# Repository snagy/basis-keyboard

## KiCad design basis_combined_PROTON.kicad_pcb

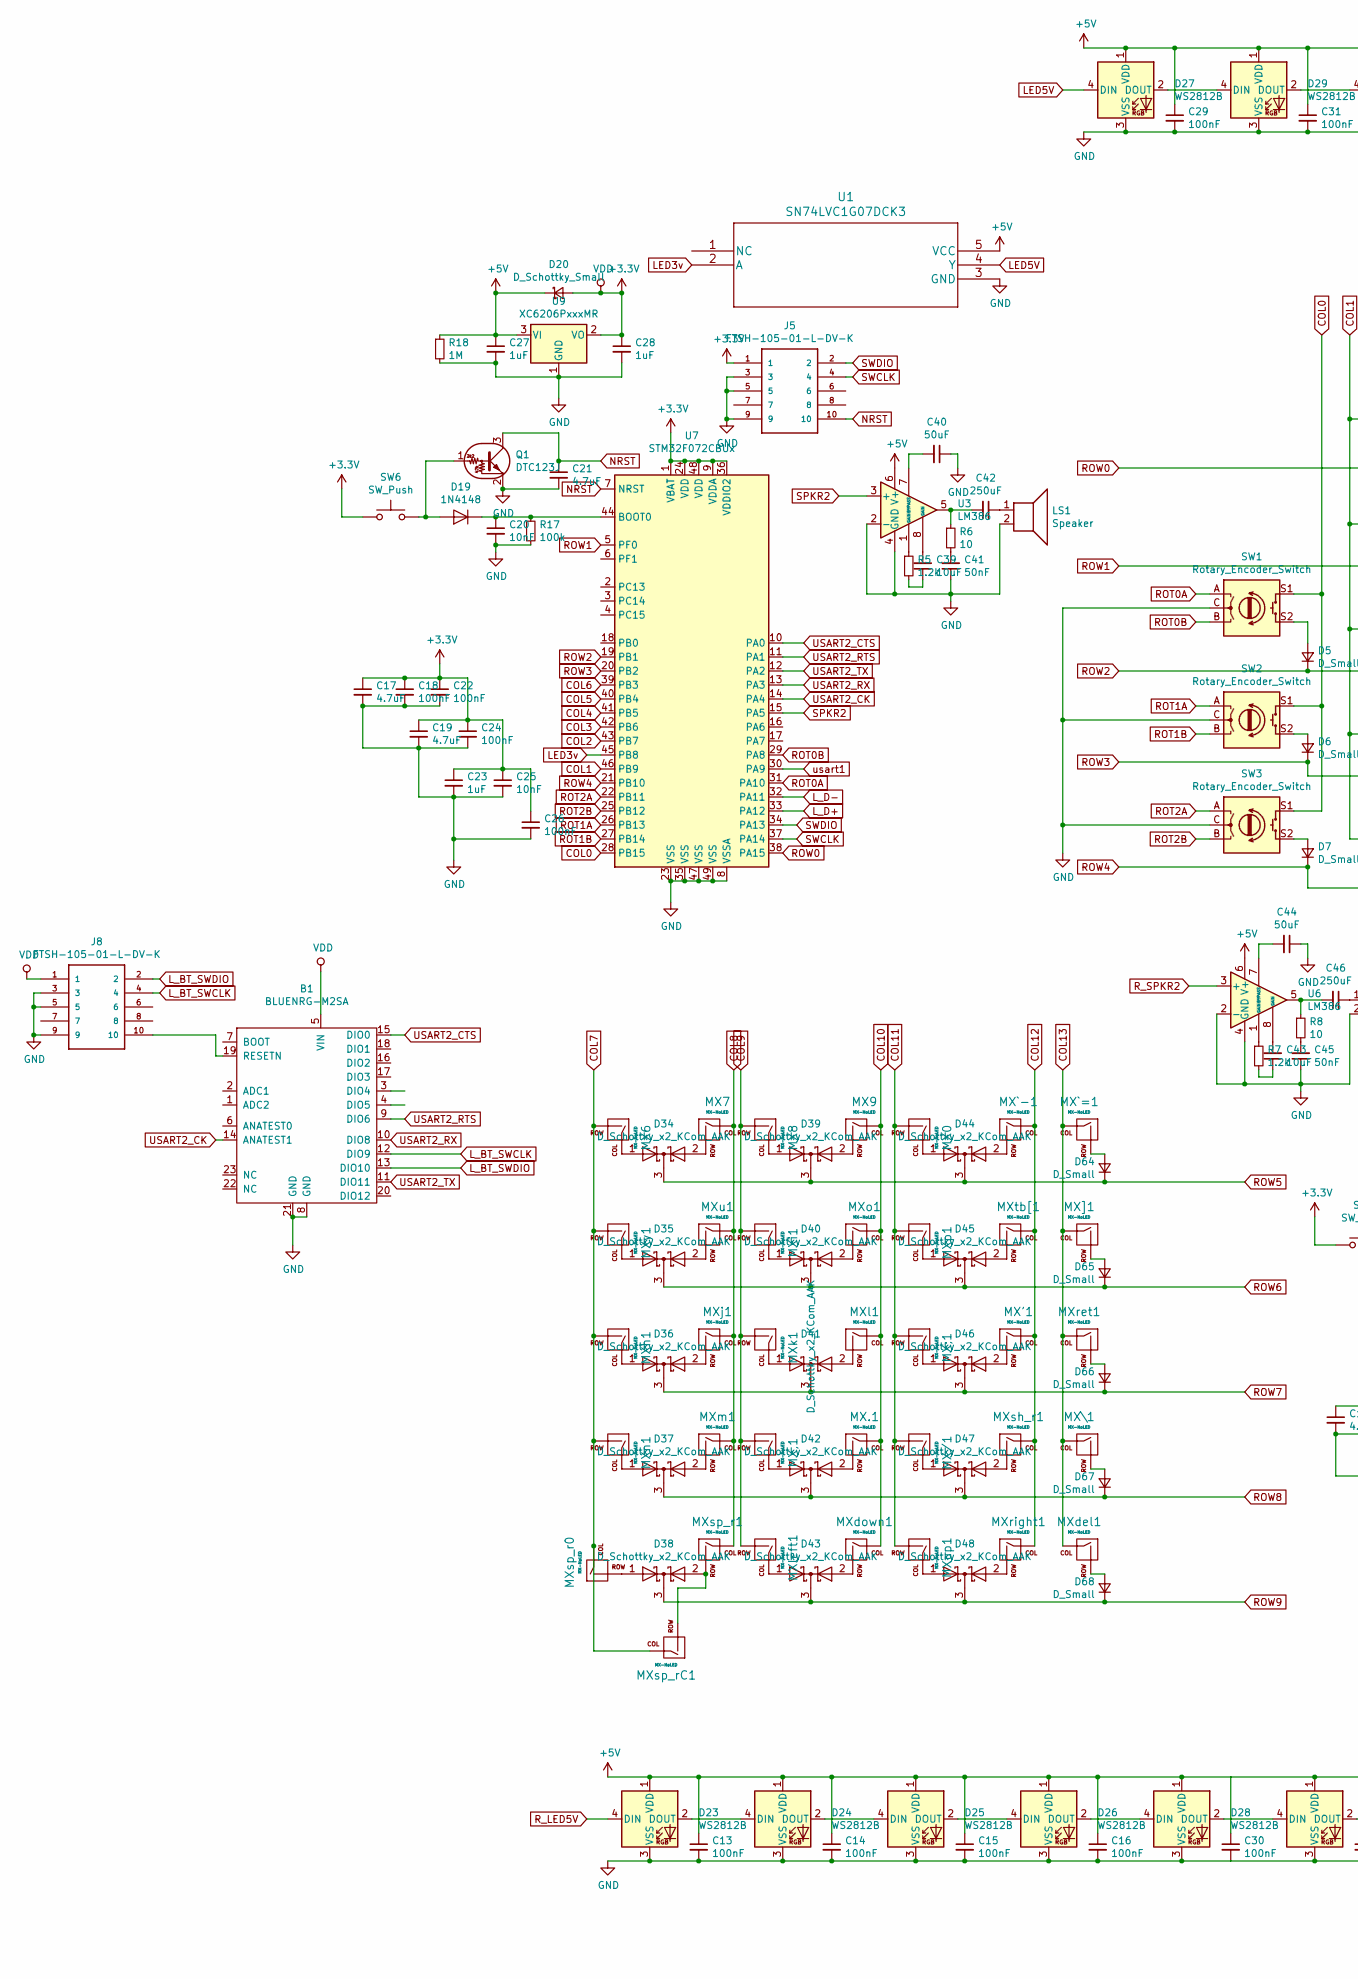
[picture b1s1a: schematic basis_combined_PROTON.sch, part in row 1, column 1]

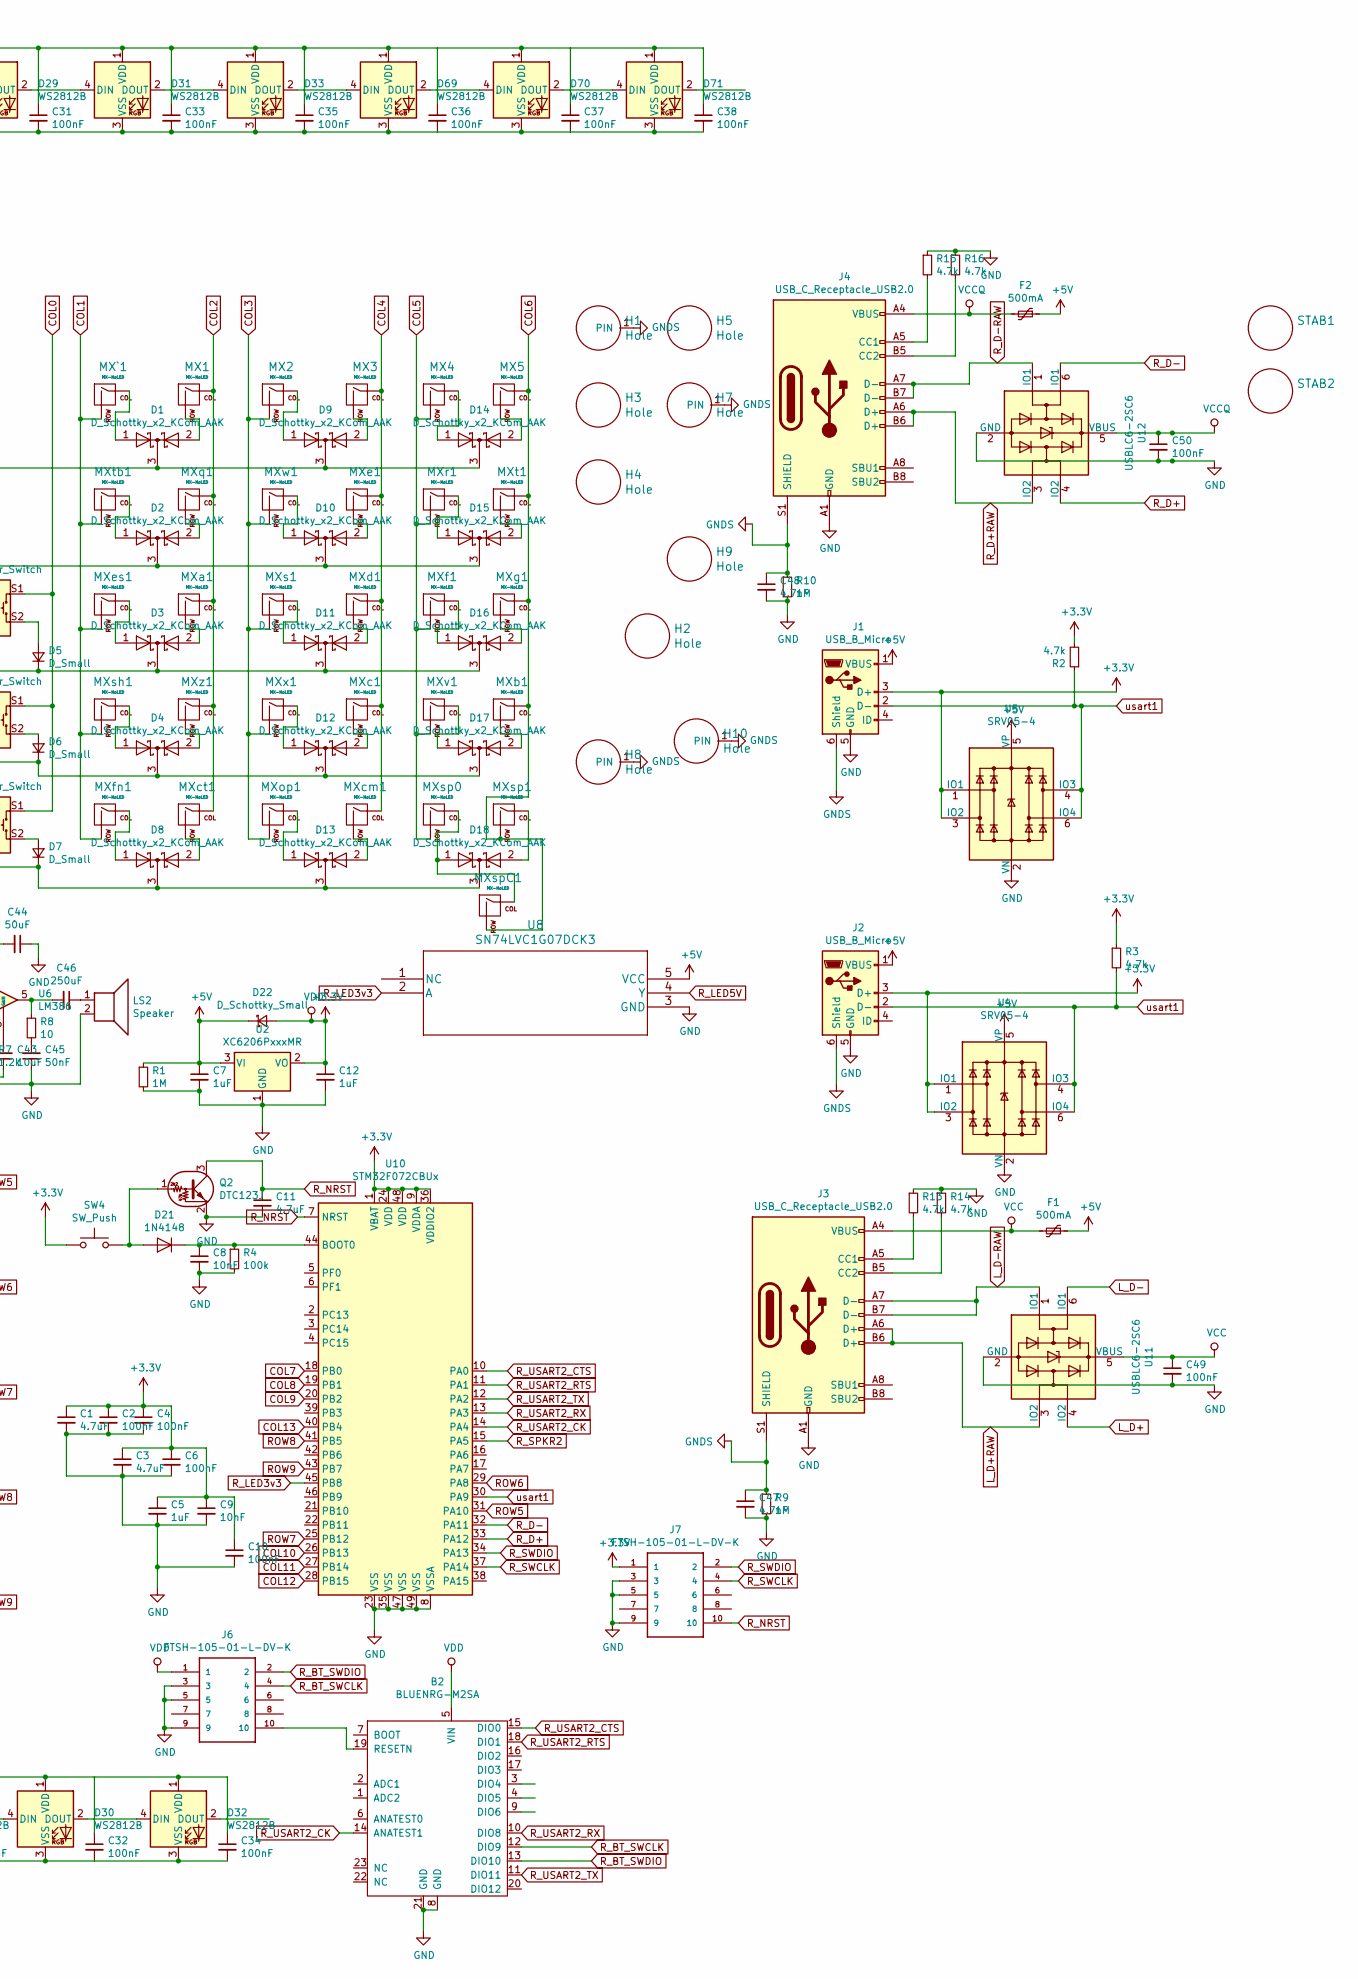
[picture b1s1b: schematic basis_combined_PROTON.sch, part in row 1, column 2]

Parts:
B1, B2: BLUENRG-M2SA
C1, C3, C11, C17, C19, C21: 4.7uF; C_0402_1005Metric
C2, C4, C6, C10, C13, C14, C15, C16, C18, C22, C24, C26, C29, C30, C31, C32, C33, C34, C35, C36, C37, C38, C49, C50: 100nF; C_0402_1005Metric
C5, C7, C12, C23, C27, C28: 1uF; C_0402_1005Metric
C8, C9, C20, C25: 10nF; C_0402_1005Metric
C39, C43: 10uF; C_0402_1005Metric
C40, C44: 50uF; C_0402_1005Metric
C41, C45: 50nF; C_0402_1005Metric
C42, C46: 250uF; C_0402_1005Metric
C47, C48: 4.7nF; C_0402_1005Metric
D1, D2, D3, D4, D8, D9, D10, D11, D12, D13, D14, D15, D16, D17, D18, D34, D35, D36, D37, D38, D39, D40, D41, D42, D43, D44, D45, D46, D47, D48: D_Schottky_x2_KCom_AAK; D_SOT-23_AAK
D5, D6, D7, D64, D65, D66, D67, D68: D_Small; D_SOD-123
D19, D21: 1N4148; D_SOD-123
D20, D22: D_Schottky_Small; D_SOD-123
D23, D24, D25, D26, D27, D28, D29, D30, D31, D32, D33, D69, D70, D71: WS2812B; LED_WS2812B_PLCC4_5.0x5.0mm_P3.2mm
F1, F2: 500mA; Fuse_1206_3216Metric
H1, H2, H3, H4, H5, H7, H8, H9, H10: Hole; Mounting_Wuerth_WA-SMSI-M2_H3.5mm_9774035243
J1, J2: USB_B_Micro; MOLEX_47642-0001
J3, J4: USB_C_Receptacle_USB2.0; USB_C_Receptacle_Hirose_CX90M-16P
J5, J6, J7, J8: FTSH-105-01-L-DV-K; SAMTEC_FTSH-105-01-L-DV-K
LS1, LS2: Speaker; cms-151103-16sp
MX0, MX1, MX2, MX3, MX4, MX5, MX6, MX7, MX8, MX9, MX.1: MX-NoLED; Kailh_socket_MX_optional
MX'1: MX-NoLED; Kailh_socket_MX_optional
MX,1: MX-NoLED; Kailh_socket_MX_optional
MX/1: MX-NoLED; Kailh_socket_MX_optional
MX;1: MX-NoLED; Kailh_socket_MX_optional
MX\1: MX-NoLED; Kailh_socket_MX_optional
MX]1: MX-NoLED; Kailh_socket_MX_optional
MX`1: MX-NoLED; Kailh_socket_MX_optional
MX`-1: MX-NoLED; Kailh_socket_MX_optional
MX`=1: MX-NoLED; Kailh_socket_MX_optional
MXa1: MX-NoLED; Kailh_socket_MX_optional
MXb1: MX-NoLED; Kailh_socket_MX_optional
MXc1: MX-NoLED; Kailh_socket_MX_optional
MXcm1: MX-NoLED; Kailh_socket_MX_optional
MXct1: MX-NoLED; Kailh_socket_MX_optional
MXd1: MX-NoLED; Kailh_socket_MX_optional
MXdel1: MX-NoLED; Kailh_socket_MX_optional
MXdown1: MX-NoLED; Kailh_socket_MX_optional
MXe1: MX-NoLED; Kailh_socket_MX_optional
MXes1: MX-NoLED; Kailh_socket_MX_optional
MXf1: MX-NoLED; Kailh_socket_MX_optional
MXfn1: MX-NoLED; Kailh_socket_MX_optional
MXg1: MX-NoLED; Kailh_socket_MX_optional
MXh1: MX-NoLED; Kailh_socket_MX_optional
MXi1: MX-NoLED; Kailh_socket_MX_optional
MXj1: MX-NoLED; Kailh_socket_MX_optional
MXk1: MX-NoLED; Kailh_socket_MX_optional
MXl1: MX-NoLED; Kailh_socket_MX_optional
MXleft1: MX-NoLED; Kailh_socket_MX_optional
MXm1: MX-NoLED; Kailh_socket_MX_optional
MXn1: MX-NoLED; Kailh_socket_MX_optional
MXo1: MX-NoLED; Kailh_socket_MX_optional
MXop1: MX-NoLED; Kailh_socket_MX_optional
MXp1: MX-NoLED; Kailh_socket_MX_optional
MXq1: MX-NoLED; Kailh_socket_MX_optional
MXr1: MX-NoLED; Kailh_socket_MX_optional
MXret1: MX-NoLED; Kailh_socket_MX_optional
MXright1: MX-NoLED; Kailh_socket_MX_optional
MXs1: MX-NoLED; Kailh_socket_MX_optional
MXsh1: MX-NoLED; Kailh_socket_MX_optional
MXsh_r1: MX-NoLED; Kailh_socket_MX_optional
MXsp0, MXsp1: MX-NoLED; Kailh_socket_MX_optional
MXspC1: MX-NoLED; Kailh_socket_MX_optional
MXsp_r0, MXsp_r1: MX-NoLED; Kailh_socket_MX_optional
MXsp_rC1: MX-NoLED; Kailh_socket_MX_optional
MXt1: MX-NoLED; Kailh_socket_MX_optional
MXtb1: MX-NoLED; Kailh_socket_MX_optional
MXtb[1: MX-NoLED; Kailh_socket_MX_optional
MXu1: MX-NoLED; Kailh_socket_MX_optional
MXup1: MX-NoLED; Kailh_socket_MX_optional
MXv1: MX-NoLED; Kailh_socket_MX_optional
MXw1: MX-NoLED; Kailh_socket_MX_optional
MXx1: MX-NoLED; Kailh_socket_MX_optional
MXy1: MX-NoLED; Kailh_socket_MX_optional
MXz1: MX-NoLED; Kailh_socket_MX_optional
Q1, Q2: DTC123J; SOT-723
R1, R9, R10, R18: 1M; R_0402_1005Metric
R2, R3, R13, R14, R15, R16: 4.7k; R_0402_1005Metric
R4, R17: 100k; R_0402_1005Metric
R5, R7: 1.2k; R_0402_1005Metric
R6, R8: 10; R_0402_1005Metric
STAB1, STAB2: Hole; Stabilizer_MX_2u
SW1, SW2, SW3: Rotary_Encoder_Switch; RotaryEncoder_Alps_EC11E-Switch_Vertical_H20mm
SW4, SW6: SW_Push; SKQG-1155865
U1, U8: SN74LVC1G07DCK3
U2, U9: XC6206PxxxMR; SOT-23
U3, U6: LM386; SOIC-8_3.9x4.9mm_P1.27mm
U4, U5: SRV05-4; SOT-23-6
U7, U10: STM32F072CBUx; QFN-48-1EP_7x7mm_P0.5mm_EP5.6x5.6mm
U11, U12: USBLC6-2SC6; SOT-666

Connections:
+3V3: B1.5 (VIN), B2.5 (VIN), C1.1, C2.1, C3.1, C4.1, C5.1, C6.1, C9.1, C10.1, C12.1, C17.1, C18.1, C19.1, C22.1, C23.1, C24.1, C25.1, C26.1, C28.1, D20.2 (A), D22.2 (A), J1.3 (D+), J2.3 (D+), J5.1, J6.1, J7.1, J8.1, R2.2, R3.1, SW4.1, SW6.1, U2.2 (VO), U4.1 (IO1), U4.3 (IO2), U5.1 (IO1), U5.3 (IO2), U7.1 (VBAT), U7.9 (VDDA), U7.24 (VDD), U7.36 (VDDIO2), U7.48 (VDD), U9.2 (VO), U10.1 (VBAT), U10.9 (VDDA), U10.24 (VDD), U10.36 (VDDIO2), U10.48 (VDD)
+5V: C7.1, C13.1, C14.1, C15.1, C16.1, C27.1, C29.1, C30.1, C31.1, C32.1, C33.1, C34.1, C35.1, C36.1, C37.1, C38.1, D20.1 (K), D22.1 (K), D23.1 (VDD), D24.1 (VDD), D25.1 (VDD), D26.1 (VDD), D27.1 (VDD), D28.1 (VDD), D29.1 (VDD), D30.1 (VDD), D31.1 (VDD), D32.1 (VDD), D33.1 (VDD), D69.1 (VDD), D70.1 (VDD), D71.1 (VDD), F1.1, F2.1, J1.1 (VBUS), J2.1 (VBUS), R1.1, R18.1, U1.5 (VCC), U2.3 (VI), U3.6 (V+), U4.5 (VP), U5.5 (VP), U6.6 (V+), U8.5 (VCC), U9.3 (VI)
COL0: SW1.S1, SW2.S1, SW3.S1, U7.28 (PB15)
COL1: MX`1.2 (ROW), MXes1.2 (ROW), MXfn1.2 (ROW), MXsh1.2 (ROW), MXtb1.2 (ROW), U7.46 (PB9)
COL2: MX1.1 (COL), MXa1.1 (COL), MXct1.1 (COL), MXq1.1 (COL), MXz1.1 (COL), U7.43 (PB7)
COL3: MX2.2 (ROW), MXop1.2 (ROW), MXs1.2 (ROW), MXw1.2 (ROW), MXx1.2 (ROW), U7.42 (PB6)
COL4: MX3.1 (COL), MXc1.1 (COL), MXcm1.1 (COL), MXd1.1 (COL), MXe1.1 (COL), U7.41 (PB5)
COL5: MX4.2 (ROW), MXf1.2 (ROW), MXr1.2 (ROW), MXsp0.2 (ROW), MXv1.2 (ROW), U7.40 (PB4)
COL6: MX5.1 (COL), MXb1.1 (COL), MXg1.1 (COL), MXsp1.2 (ROW), MXspC1.2 (ROW), MXt1.1 (COL), U7.39 (PB3)
COL7: MX6.2 (ROW), MXh1.2 (ROW), MXn1.2 (ROW), MXsp_r0.1 (COL), MXsp_rC1.1 (COL), MXy1.2 (ROW), U10.18 (PB0)
COL8: MX7.1 (COL), MXj1.1 (COL), MXm1.1 (COL), MXsp_r1.1 (COL), MXu1.1 (COL), U10.19 (PB1)
COL9: MX8.2 (ROW), MX,1.2 (ROW), MXi1.2 (ROW), MXk1.2 (ROW), MXleft1.2 (ROW), U10.20 (PB2)
COL10: MX9.1 (COL), MX.1.1 (COL), MXdown1.1 (COL), MXl1.1 (COL), MXo1.1 (COL), U10.26 (PB13)
COL11: MX0.2 (ROW), MX/1.2 (ROW), MX;1.2 (ROW), MXp1.2 (ROW), MXup1.2 (ROW), U10.27 (PB14)
COL12: MX'1.1 (COL), MX`-1.1 (COL), MXright1.1 (COL), MXsh_r1.1 (COL), MXtb[1.1 (COL), U10.28 (PB15)
COL13: MX\1.1 (COL), MX]1.1 (COL), MX`=1.1 (COL), MXdel1.1 (COL), MXret1.1 (COL), U10.40 (PB4)
GND: B1.8 (GND), B1.21 (GND), B2.8 (GND), B2.21 (GND), C1.2, C2.2, C3.2, C4.2, C5.2, C6.2, C7.2, C8.2, C9.2, C10.2, C11.2, C12.2, C13.2, C14.2, C15.2, C16.2, C17.2, C18.2, C19.2, C20.2, C21.2, C22.2, C23.2, C24.2, C25.2, C26.2, C27.2, C28.2, C29.2, C30.2, C31.2, C32.2, C33.2, C34.2, C35.2, C36.2, C37.2, C38.2, C40.1, C41.1, C44.1, C45.1, C47.2, C48.2, C49.2, C50.2, D23.3 (VSS), D24.3 (VSS), D25.3 (VSS), D26.3 (VSS), D27.3 (VSS), D28.3 (VSS), D29.3 (VSS), D30.3 (VSS), D31.3 (VSS), D32.3 (VSS), D33.3 (VSS), D69.3 (VSS), D70.3 (VSS), D71.3 (VSS), J1.5 (GND), J2.5 (GND), J3.A1 (GND), J3.A12 (GND), J3.B1 (GND), J3.B12 (GND), J4.A1 (GND), J4.A12 (GND), J4.B1 (GND), J4.B12 (GND), J5.3, J5.5, J5.9, J6.3, J6.5, J6.9, J7.3, J7.5, J7.9, J8.3, J8.5, J8.9, LS1.2, LS2.2, Q1.2 (E), Q2.2 (E), R1.2, R4.2, R9.2, R10.2, R13.1, R14.1, R15.1, R16.1, R17.2, R18.2, SW1.C, SW2.C, SW3.C, U1.3 (GND), U2.1 (GND), U3.2 (-), U3.4 (GND), U4.2 (VN), U5.2 (VN), U6.2 (-), U6.4 (GND), U7.8 (VSSA), U7.23 (VSS), U7.35 (VSS), U7.47 (VSS), U7.49 (VSS), U8.3 (GND), U9.1 (GND), U10.8 (VSSA), U10.23 (VSS), U10.35 (VSS), U10.47 (VSS), U10.49 (VSS), U11.2 (GND), U12.2 (GND)
GNDS: C47.1, C48.1, H1.1, H7.1, H8.1, H10.1, J1.6 (Shield), J2.6 (Shield), J3.S1 (SHIELD), J4.S1 (SHIELD), R9.1, R10.1
LED3v: U1.2 (A), U7.45 (PB8)
LED5V: D27.4 (DIN), U1.4 (Y)
L_BT_SWCLK: B1.12 (DIO9), J8.4
L_BT_SWDIO: B1.13 (DIO10), J8.2
L_D+: U7.33 (PA12), U11.4 (IO2)
L_D+RAW: J3.A6 (D+), J3.B6 (D+), U11.3 (IO2)
L_D-: U7.32 (PA11), U11.6 (IO1)
L_D-RAW: J3.A7 (D-), J3.B7 (D-), U11.1 (IO1)
NRST: C21.1, J5.10, Q1.3 (C), U7.7 (NRST)
unnamed: B1.19 (RESETN), J8.10
unnamed: B2.19 (RESETN), J6.10
unnamed: C8.1, D21.1 (K), R4.1, U10.44 (BOOT0)
unnamed: C20.1, D19.1 (K), R17.1, U7.44 (BOOT0)
unnamed: C39.1, R5.2
unnamed: C39.2, U3.8 (GAIN)
unnamed: C40.2, U3.7 (BYPASS)
unnamed: C41.2, R6.2
unnamed: C42.1, LS1.1
unnamed: C42.2, R6.1, U3.5
unnamed: C43.1, R7.2
unnamed: C43.2, U6.8 (GAIN)
unnamed: C44.2, U6.7 (BYPASS)
unnamed: C45.2, R8.2
unnamed: C46.1, LS2.1
unnamed: C46.2, R8.1, U6.5
unnamed: D1.1 (A), MX`1.1 (COL)
unnamed: D1.2 (A), MX1.2 (ROW)
unnamed: D2.1 (A), MXtb1.1 (COL)
unnamed: D2.2 (A), MXq1.2 (ROW)
unnamed: D3.1 (A), MXes1.1 (COL)
unnamed: D3.2 (A), MXa1.2 (ROW)
unnamed: D4.1 (A), MXsh1.1 (COL)
unnamed: D4.2 (A), MXz1.2 (ROW)
unnamed: D5.2 (A), SW1.S2
unnamed: D6.2 (A), SW2.S2
unnamed: D7.2 (A), SW3.S2
unnamed: D8.1 (A), MXfn1.1 (COL)
unnamed: D8.2 (A), MXct1.2 (ROW)
unnamed: D9.1 (A), MX2.1 (COL)
unnamed: D9.2 (A), MX3.2 (ROW)
unnamed: D10.1 (A), MXw1.1 (COL)
unnamed: D10.2 (A), MXe1.2 (ROW)
unnamed: D11.1 (A), MXs1.1 (COL)
unnamed: D11.2 (A), MXd1.2 (ROW)
unnamed: D12.1 (A), MXx1.1 (COL)
unnamed: D12.2 (A), MXc1.2 (ROW)
unnamed: D13.1 (A), MXop1.1 (COL)
unnamed: D13.2 (A), MXcm1.2 (ROW)
unnamed: D14.1 (A), MX4.1 (COL)
unnamed: D14.2 (A), MX5.2 (ROW)
unnamed: D15.1 (A), MXr1.1 (COL)
unnamed: D15.2 (A), MXt1.2 (ROW)
unnamed: D16.1 (A), MXf1.1 (COL)
unnamed: D16.2 (A), MXg1.2 (ROW)
unnamed: D17.1 (A), MXv1.1 (COL)
unnamed: D17.2 (A), MXb1.2 (ROW)
unnamed: D18.1 (A), MXsp0.1 (COL), MXspC1.1 (COL)
unnamed: D18.2 (A), MXsp1.1 (COL)
unnamed: D19.2 (A), Q1.1 (B), SW6.2
unnamed: D21.2 (A), Q2.1 (B), SW4.2
unnamed: D23.2 (DOUT), D24.4 (DIN)
unnamed: D24.2 (DOUT), D25.4 (DIN)
unnamed: D25.2 (DOUT), D26.4 (DIN)
unnamed: D26.2 (DOUT), D28.4 (DIN)
unnamed: D27.2 (DOUT), D29.4 (DIN)
unnamed: D28.2 (DOUT), D30.4 (DIN)
unnamed: D29.2 (DOUT), D31.4 (DIN)
unnamed: D30.2 (DOUT), D32.4 (DIN)
unnamed: D31.2 (DOUT), D33.4 (DIN)
unnamed: D33.2 (DOUT), D69.4 (DIN)
unnamed: D34.1 (A), MX6.1 (COL)
unnamed: D34.2 (A), MX7.2 (ROW)
unnamed: D35.1 (A), MXy1.1 (COL)
unnamed: D35.2 (A), MXu1.2 (ROW)
unnamed: D36.1 (A), MXh1.1 (COL)
unnamed: D36.2 (A), MXj1.2 (ROW)
unnamed: D37.1 (A), MXn1.1 (COL)
unnamed: D37.2 (A), MXm1.2 (ROW)
unnamed: D38.1 (A), MXsp_r0.2 (ROW)
unnamed: D38.2 (A), MXsp_r1.2 (ROW), MXsp_rC1.2 (ROW)
unnamed: D39.1 (A), MX8.1 (COL)
unnamed: D39.2 (A), MX9.2 (ROW)
unnamed: D40.1 (A), MXi1.1 (COL)
unnamed: D40.2 (A), MXo1.2 (ROW)
unnamed: D41.1 (A), MXk1.1 (COL)
unnamed: D41.2 (A), MXl1.2 (ROW)
unnamed: D42.1 (A), MX,1.1 (COL)
unnamed: D42.2 (A), MX.1.2 (ROW)
unnamed: D43.1 (A), MXleft1.1 (COL)
unnamed: D43.2 (A), MXdown1.2 (ROW)
unnamed: D44.1 (A), MX0.1 (COL)
unnamed: D44.2 (A), MX`-1.2 (ROW)
unnamed: D45.1 (A), MXp1.1 (COL)
unnamed: D45.2 (A), MXtb[1.2 (ROW)
unnamed: D46.1 (A), MX;1.1 (COL)
unnamed: D46.2 (A), MX'1.2 (ROW)
unnamed: D47.1 (A), MX/1.1 (COL)
unnamed: D47.2 (A), MXsh_r1.2 (ROW)
unnamed: D48.1 (A), MXup1.1 (COL)
unnamed: D48.2 (A), MXright1.2 (ROW)
unnamed: D64.2 (A), MX`=1.2 (ROW)
unnamed: D65.2 (A), MX]1.2 (ROW)
unnamed: D66.2 (A), MXret1.2 (ROW)
unnamed: D67.2 (A), MX\1.2 (ROW)
unnamed: D68.2 (A), MXdel1.2 (ROW)
unnamed: D69.2 (DOUT), D70.4 (DIN)
unnamed: D70.2 (DOUT), D71.4 (DIN)
unnamed: J3.A5 (CC1), R13.2
unnamed: J3.B5 (CC2), R14.2
unnamed: J4.A5 (CC1), R15.2
unnamed: J4.B5 (CC2), R16.2
unnamed: R5.1, U3.1 (GAIN)
unnamed: R7.1, U6.1 (GAIN)
ROT0A: SW1.A, U7.31 (PA10)
ROT0B: SW1.B, U7.29 (PA8)
ROT1A: SW2.A, U7.26 (PB13)
ROT1B: SW2.B, U7.27 (PB14)
ROT2A: SW3.A, U7.22 (PB11)
ROT2B: SW3.B, U7.25 (PB12)
ROW0: D1.3 (K), D9.3 (K), D14.3 (K), U7.38 (PA15)
ROW1: D2.3 (K), D10.3 (K), D15.3 (K), U7.5 (PF0)
ROW2: D3.3 (K), D5.1 (K), D11.3 (K), D16.3 (K), U7.19 (PB1)
ROW3: D4.3 (K), D6.1 (K), D12.3 (K), D17.3 (K), U7.20 (PB2)
ROW4: D7.1 (K), D8.3 (K), D13.3 (K), D18.3 (K), U7.21 (PB10)
ROW5: D34.3 (K), D39.3 (K), D44.3 (K), D64.1 (K), U10.31 (PA10)
ROW6: D35.3 (K), D40.3 (K), D45.3 (K), D65.1 (K), U10.29 (PA8)
ROW7: D36.3 (K), D41.3 (K), D46.3 (K), D66.1 (K), U10.25 (PB12)
ROW8: D37.3 (K), D42.3 (K), D47.3 (K), D67.1 (K), U10.41 (PB5)
ROW9: D38.3 (K), D43.3 (K), D48.3 (K), D68.1 (K), U10.43 (PB7)
R_BT_SWCLK: B2.12 (DIO9), J6.4
R_BT_SWDIO: B2.13 (DIO10), J6.2
R_D+: U10.33 (PA12), U12.4 (IO2)
R_D+RAW: J4.A6 (D+), J4.B6 (D+), U12.3 (IO2)
R_D-: U10.32 (PA11), U12.6 (IO1)
R_D-RAW: J4.A7 (D-), J4.B7 (D-), U12.1 (IO1)
R_LED3v3: U8.2 (A), U10.45 (PB8)
R_LED5V: D23.4 (DIN), U8.4 (Y)
R_NRST: C11.1, J7.10, Q2.3 (C), U10.7 (NRST)
R_SPKR2: U6.3 (+), U10.15 (PA5)
R_SWCLK: J7.4, U10.37 (PA14)
R_SWDIO: J7.2, U10.34 (PA13)
R_USART2_CK: B2.14 (ANATEST1), U10.14 (PA4)
R_USART2_CTS: B2.15 (DIO0), U10.10 (PA0)
R_USART2_RTS: B2.18 (DIO1), U10.11 (PA1)
R_USART2_RX: B2.10 (DIO8), U10.13 (PA3)
R_USART2_TX: B2.11 (DIO11), U10.12 (PA2)
SPKR2: U3.3 (+), U7.15 (PA5)
SWCLK: J5.4, U7.37 (PA14)
SWDIO: J5.2, U7.34 (PA13)
USART2_CK: B1.14 (ANATEST1), U7.14 (PA4)
USART2_CTS: B1.15 (DIO0), U7.10 (PA0)
USART2_RTS: B1.9 (DIO6), U7.11 (PA1)
USART2_RX: B1.10 (DIO8), U7.13 (PA3)
USART2_TX: B1.11 (DIO11), U7.12 (PA2)
VCC: C49.1, F1.2, J3.A4 (VBUS), J3.A9 (VBUS), J3.B4 (VBUS), J3.B9 (VBUS), U11.5 (VBUS)
VCCQ: C50.1, F2.2, J4.A4 (VBUS), J4.A9 (VBUS), J4.B4 (VBUS), J4.B9 (VBUS), U12.5 (VBUS)
usart1: J1.2 (D-), J2.2 (D-), R2.1, R3.2, U4.4 (IO3), U4.6 (IO4), U5.4 (IO3), U5.6 (IO4), U7.30 (PA9), U10.30 (PA9)

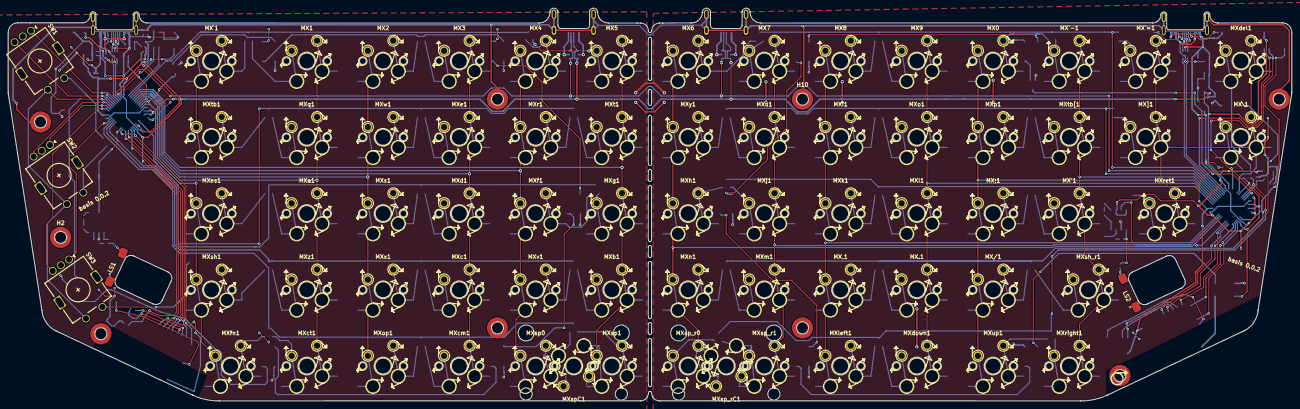
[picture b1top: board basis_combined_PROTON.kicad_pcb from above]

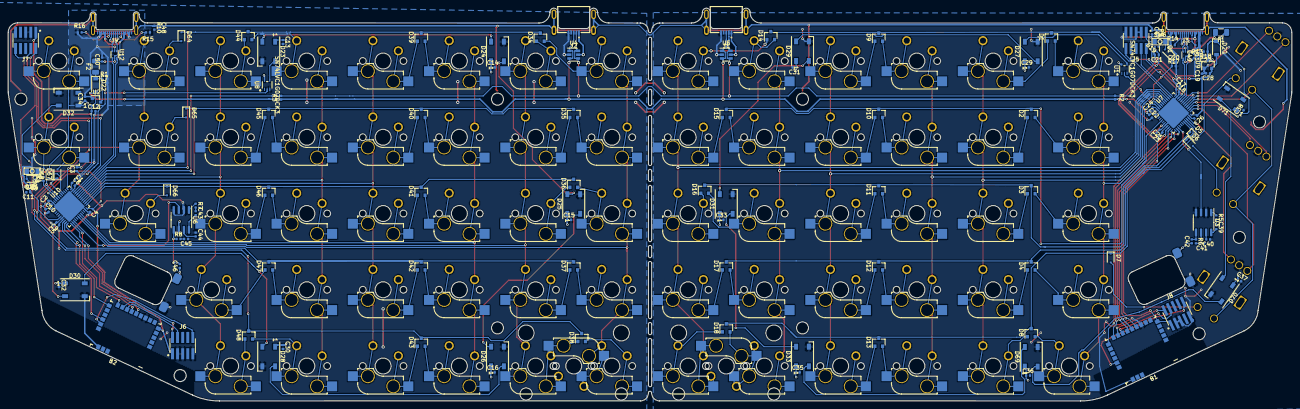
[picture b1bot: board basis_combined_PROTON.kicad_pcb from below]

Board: 2 copper layers, 320.7 x 98.1 mm, 233 parts (150 on the bottom side), 175 nets.

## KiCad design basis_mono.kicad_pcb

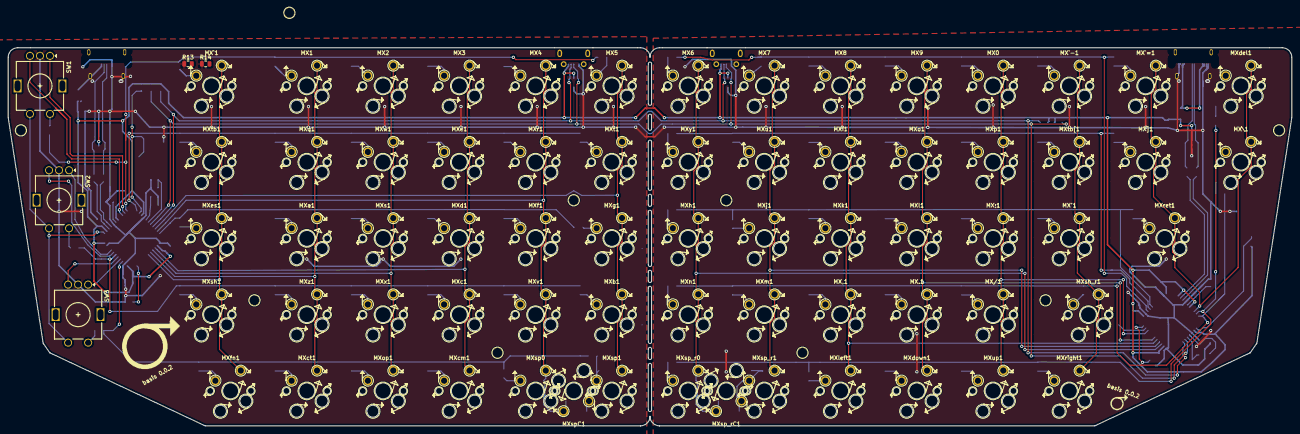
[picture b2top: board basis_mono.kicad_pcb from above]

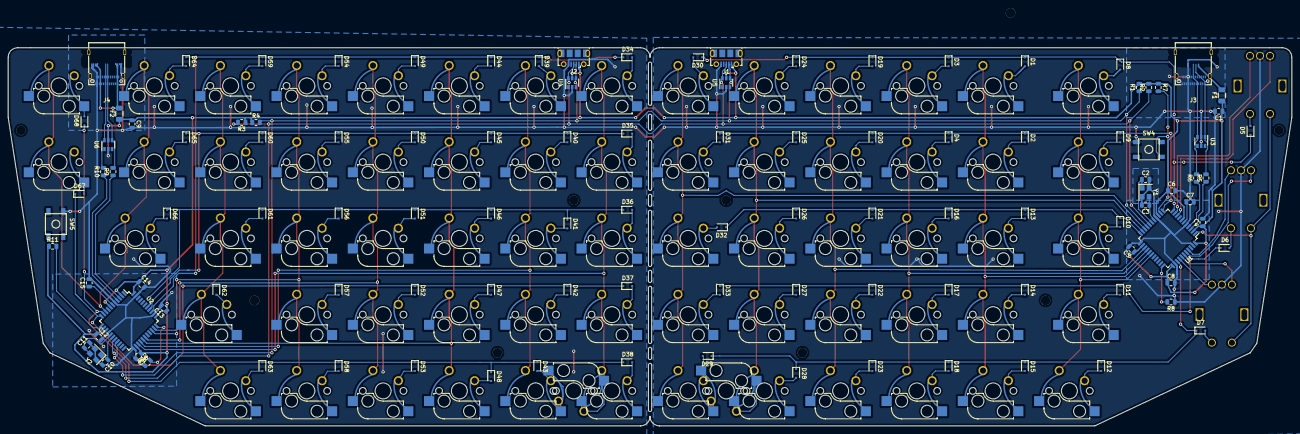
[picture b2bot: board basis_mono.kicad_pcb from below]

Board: 2 copper layers, 320.7 x 94.5 mm, 193 parts (112 on the bottom side), 122 nets.

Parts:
C1, C9: 10uf; C_0805_2012Metric
C2, C3, C10, C11: 22pF; C_0805_2012Metric
C4, C12: 0.1uF; C_0805_2012Metric
C5, C6, C8, C13, C14, C16: 0.1uf; C_0805_2012Metric
C7, C15: 1uF; C_0805_2012Metric
D1, D2, D3, D4, D5, D6, D7, D8, D9, D10, D11, D12, D13, D14, D15, D16, D17, D18, D19, D20, D21, D22, D23, D24, D25, D26, D27, D28, D29, D30, D31, D32, D33, D34, D35, D36, D37, D38, D39, D40, D41, D42, D43, D44, D45, D46, D47, D48, D49, D50, D51, D52, D53, D54, D55, D56, D57, D58, D59, D60, D61, D62, D63, D64, D65, D66, D67, D68: D_Small; D_SOD-323F
F1, F2: 500mA; Fuse_1206_3216Metric
H1, H2, H3, H4, H5, H6, H7, H8, H9: Hole; MountingHole-m2
J1, J2: USB_B_Micro; USB_Micro-B_Molex-105017-0001
J3, J4: USB_C_Receptacle_USB2.0; AMPHENOL_12401598E4#2A
MX0, MX1, MX2, MX3, MX4, MX5, MX6, MX7, MX8, MX9, MX.1: MX-NoLED; Kailh_socket_MX_optional_FLIPPED_COPPER
MX'1: MX-NoLED; Kailh_socket_MX_optional_FLIPPED_COPPER
MX,1: MX-NoLED; Kailh_socket_MX_optional_FLIPPED_COPPER
MX/1: MX-NoLED; Kailh_socket_MX_optional_FLIPPED_COPPER
MX;1: MX-NoLED; Kailh_socket_MX_optional_FLIPPED_COPPER
MX\1: MX-NoLED; Kailh_socket_MX_optional_FLIPPED_COPPER
MX]1: MX-NoLED; Kailh_socket_MX_optional_FLIPPED_COPPER
MX`1: MX-NoLED; Kailh_socket_MX_optional_FLIPPED_COPPER
MX`-1: MX-NoLED; Kailh_socket_MX_optional_FLIPPED_COPPER
MX`=1: MX-NoLED; Kailh_socket_MX_optional_FLIPPED_COPPER
MXa1: MX-NoLED; Kailh_socket_MX_optional_FLIPPED_COPPER
MXb1: MX-NoLED; Kailh_socket_MX_optional_FLIPPED_COPPER
MXc1: MX-NoLED; Kailh_socket_MX_optional_FLIPPED_COPPER
MXcm1: MX-NoLED; Kailh_socket_MX_optional_FLIPPED_COPPER
MXct1: MX-NoLED; Kailh_socket_MX_optional_FLIPPED_COPPER
MXd1: MX-NoLED; Kailh_socket_MX_optional_FLIPPED_COPPER
MXdel1: MX-NoLED; Kailh_socket_MX_optional_FLIPPED_COPPER
MXdown1: MX-NoLED; Kailh_socket_MX_optional_FLIPPED_COPPER
MXe1: MX-NoLED; Kailh_socket_MX_optional_FLIPPED_COPPER
MXes1: MX-NoLED; Kailh_socket_MX_optional_FLIPPED_COPPER
MXf1: MX-NoLED; Kailh_socket_MX_optional_FLIPPED_COPPER
MXfn1: MX-NoLED; Kailh_socket_MX_optional_FLIPPED_COPPER
MXg1: MX-NoLED; Kailh_socket_MX_optional_FLIPPED_COPPER
MXh1: MX-NoLED; Kailh_socket_MX_optional_FLIPPED_COPPER
MXi1: MX-NoLED; Kailh_socket_MX_optional_FLIPPED_COPPER
MXj1: MX-NoLED; Kailh_socket_MX_optional_FLIPPED_COPPER
MXk1: MX-NoLED; Kailh_socket_MX_optional_FLIPPED_COPPER
MXl1: MX-NoLED; Kailh_socket_MX_optional_FLIPPED_COPPER
MXleft1: MX-NoLED; Kailh_socket_MX_optional_FLIPPED_COPPER
MXm1: MX-NoLED; Kailh_socket_MX_optional_FLIPPED_COPPER
MXn1: MX-NoLED; Kailh_socket_MX_optional_FLIPPED_COPPER
MXo1: MX-NoLED; Kailh_socket_MX_optional_FLIPPED_COPPER
MXop1: MX-NoLED; Kailh_socket_MX_optional_FLIPPED_COPPER
MXp1: MX-NoLED; Kailh_socket_MX_optional_FLIPPED_COPPER
MXq1: MX-NoLED; Kailh_socket_MX_optional_FLIPPED_COPPER
MXr1: MX-NoLED; Kailh_socket_MX_optional_FLIPPED_COPPER
MXret1: MX-NoLED; Kailh_socket_MX_optional_FLIPPED_COPPER
MXright1: MX-NoLED; Kailh_socket_MX_optional_FLIPPED_COPPER
MXs1: MX-NoLED; Kailh_socket_MX_optional_FLIPPED_COPPER
MXsh1: MX-NoLED; Kailh_socket_MX_optional_FLIPPED_COPPER
MXsh_r1: MX-NoLED; Kailh_socket_MX_optional_FLIPPED_COPPER
MXsp0, MXsp1: MX-NoLED; Kailh_socket_MX_optional_FLIPPED_COPPER
MXspC1: MX-NoLED; Kailh_socket_MX_optional_FLIPPED_COPPER
MXsp_r0, MXsp_r1: MX-NoLED; Kailh_socket_MX_optional_FLIPPED_COPPER
MXsp_rC1: MX-NoLED; Kailh_socket_MX_optional_FLIPPED_COPPER
MXt1: MX-NoLED; Kailh_socket_MX_optional_FLIPPED_COPPER
MXtb1: MX-NoLED; Kailh_socket_MX_optional_FLIPPED_COPPER
MXtb[1: MX-NoLED; Kailh_socket_MX_optional_FLIPPED_COPPER
MXu1: MX-NoLED; Kailh_socket_MX_optional_FLIPPED_COPPER
MXup1: MX-NoLED; Kailh_socket_MX_optional_FLIPPED_COPPER
MXv1: MX-NoLED; Kailh_socket_MX_optional_FLIPPED_COPPER
MXw1: MX-NoLED; Kailh_socket_MX_optional_FLIPPED_COPPER
MXx1: MX-NoLED; Kailh_socket_MX_optional_FLIPPED_COPPER
MXy1: MX-NoLED; Kailh_socket_MX_optional_FLIPPED_COPPER
MXz1: MX-NoLED; Kailh_socket_MX_optional_FLIPPED_COPPER
R1, R2, R3, R4, R13, R14: 4.7k; R_0805_2012Metric
R5, R6, R9, R10: 22; R_0805_2012Metric
R7, R8, R11, R12: 10k; R_0805_2012Metric
SW1, SW2, SW3: Rotary_Encoder_Switch; Rotary_encoder_switch_HOTSWAP
SW4, SW5: SW_Push; SKQG-1155865
U1, U2: ATmega32U4-AU; TQFP-44_10x10mm_P0.8mm
U3, U4, U5, U6: SRV05-4; SOT-23-6
Y1, Y2: Crystal_GND24_Small; Crystal_SMD_3225-4Pin_3.2x2.5mm

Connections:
+5V: C1.1, C4.1, C5.1, C6.1, C8.1, C9.1, C12.1, C13.1, C14.1, C16.1, F1.1, F2.1, J1.1, J2.1, R1.2, R2.2, R3.1, R4.1, R7.1, R11.1, U1.2, U1.7, U1.14, U1.24, U1.34, U1.44, U2.2, U2.7, U2.14, U2.24, U2.34, U2.44, U3.5, U4.5, U5.5, U6.5
COL0: SW1.S1, SW2.S1, SW3.S1, U1.1
COL1: MX`1.1, MXes1.1, MXfn1.1, MXsh1.1, MXtb1.1, U1.28
COL2: MX1.1, MXa1.1, MXct1.1, MXq1.1, MXz1.1, U1.27
COL3: MX2.1, MXop1.1, MXs1.1, MXw1.1, MXx1.1, U1.26
COL4: MX3.1, MXc1.1, MXcm1.1, MXd1.1, MXe1.1, U1.25
COL5: MX4.1, MXf1.1, MXr1.1, MXsp0.1, MXspC1.1, MXv1.1, U1.21
COL6: MX5.1, MXb1.1, MXg1.1, MXsp1.1, MXt1.1, U1.20
COL7: MX6.1, MXh1.1, MXn1.1, MXsp_r0.1, MXsp_rC1.1, MXy1.1, U2.25
COL8: MX7.1, MXj1.1, MXm1.1, MXsp_r1.1, MXu1.1, U2.26
COL9: MX8.1, MX,1.1, MXi1.1, MXk1.1, MXleft1.1, U2.27
COL10: MX9.1, MX.1.1, MXdown1.1, MXl1.1, MXo1.1, U2.28
COL11: MX0.1, MX/1.1, MX;1.1, MXp1.1, MXup1.1, U2.31
COL12: MX'1.1, MX`-1.1, MXright1.1, MXsh_r1.1, MXtb[1.1, U2.32
COL13: MX\1.1, MX]1.1, MX`=1.1, MXdel1.1, MXret1.1, U2.9
D+: J3.A6, J3.B6, J4.A6, J4.B6, R6.2, R10.2, U3.3, U3.6, U6.3, U6.6
D-: J3.A7, J3.B7, J4.A7, J4.B7, R5.2, R9.2, U3.1, U3.4, U6.1, U6.4
GND: C1.2, C2.2, C3.2, C4.2, C5.2, C6.2, C7.2, C8.2, C9.2, C10.2, C11.2, C12.2, C13.2, C14.2, C15.2, C16.2, J1.5, J2.5, J3.A1, J3.A12, J3.B1, J3.B12, J4.A1, J4.A12, J4.B1, J4.B12, R8.1, R12.1, R13.1, R14.1, SW1.C, SW2.C, SW3.C, SW4.1, SW5.1, U1.5, U1.15, U1.23, U1.35, U1.43, U2.5, U2.15, U2.23, U2.35, U2.43, U3.2, U4.2, U5.2, U6.2, Y1.2, Y1.4, Y2.2, Y2.4
LED: U1.30, U2.30
unnamed: C2.1, U1.17, Y1.1
unnamed: C3.1, U1.16, Y1.3
unnamed: C7.1, U1.6
unnamed: C10.1, U2.17, Y2.1
unnamed: C11.1, U2.16, Y2.3
unnamed: C15.1, U2.6
unnamed: D1.2, MX1.2
unnamed: D2.2, MXq1.2
unnamed: D3.2, MX2.2
unnamed: D4.2, MXw1.2
unnamed: D5.2, SW1.S2
unnamed: D6.2, SW2.S2
unnamed: D7.2, SW3.S2
unnamed: D8.2, MX`1.2
unnamed: D9.2, MXtb1.2
unnamed: D10.2, MXes1.2
unnamed: D11.2, MXsh1.2
unnamed: D12.2, MXfn1.2
unnamed: D13.2, MXa1.2
unnamed: D14.2, MXz1.2
unnamed: D15.2, MXct1.2
unnamed: D16.2, MXs1.2
unnamed: D17.2, MXx1.2
unnamed: D18.2, MXop1.2
unnamed: D19.2, MX3.2
unnamed: D20.2, MXe1.2
unnamed: D21.2, MXd1.2
unnamed: D22.2, MXc1.2
unnamed: D23.2, MXcm1.2
unnamed: D24.2, MX4.2
unnamed: D25.2, MXr1.2
unnamed: D26.2, MXf1.2
unnamed: D27.2, MXv1.2
unnamed: D28.2, MXsp0.2
unnamed: D29.2, MXsp1.2, MXspC1.2
unnamed: D30.2, MX5.2
unnamed: D31.2, MXt1.2
unnamed: D32.2, MXg1.2
unnamed: D33.2, MXb1.2
unnamed: D34.2, MX6.2
unnamed: D35.2, MXy1.2
unnamed: D36.2, MXh1.2
unnamed: D37.2, MXn1.2
unnamed: D38.2, MXsp_r0.2
unnamed: D39.2, MX7.2
unnamed: D40.2, MXu1.2
unnamed: D41.2, MXj1.2
unnamed: D42.2, MXm1.2
unnamed: D43.2, MXsp_r1.2, MXsp_rC1.2
unnamed: D44.2, MX8.2
unnamed: D45.2, MXi1.2
unnamed: D46.2, MXk1.2
unnamed: D47.2, MX,1.2
unnamed: D48.2, MXleft1.2
unnamed: D49.2, MX9.2
unnamed: D50.2, MXo1.2
unnamed: D51.2, MXl1.2
unnamed: D52.2, MX.1.2
unnamed: D53.2, MXdown1.2
unnamed: D54.2, MX0.2
unnamed: D55.2, MXp1.2
unnamed: D56.2, MX;1.2
unnamed: D57.2, MX/1.2
unnamed: D58.2, MXup1.2
unnamed: D59.2, MX`-1.2
unnamed: D60.2, MXtb[1.2
unnamed: D61.2, MX'1.2
unnamed: D62.2, MXsh_r1.2
unnamed: D63.2, MXright1.2
unnamed: D64.2, MX`=1.2
unnamed: D65.2, MX]1.2
unnamed: D66.2, MXret1.2
unnamed: D67.2, MX\1.2
unnamed: D68.2, MXdel1.2
unnamed: J3.A5, R13.2
unnamed: J3.B5, R14.2
unnamed: R5.1, U1.3
unnamed: R6.1, U1.4
unnamed: R7.2, SW4.2, U1.13
unnamed: R8.2, U1.33
unnamed: R9.1, U2.3
unnamed: R10.1, U2.4
unnamed: R11.2, SW5.2, U2.13
unnamed: R12.2, U2.33
ROT0A: SW1.A, U1.10
ROT0B: SW1.B, U1.9
ROT1A: SW2.A, U1.41
ROT1B: SW2.B, U1.40
ROT2A: SW3.A, U1.37
ROT2B: SW3.B, U1.38
ROW0: D1.1, D3.1, D5.1, D8.1, D19.1, D24.1, D30.1, U1.11
ROW1: D2.1, D4.1, D9.1, D20.1, D25.1, D31.1, U1.12
ROW2: D10.1, D13.1, D16.1, D21.1, D26.1, D32.1, U1.22
ROW3: D6.1, D11.1, D14.1, D17.1, D22.1, D27.1, D33.1, U1.39
ROW4: D7.1, D12.1, D15.1, D18.1, D23.1, D28.1, D29.1, U1.36
ROW5: D34.1, D39.1, D44.1, D49.1, D54.1, D59.1, D64.1, U2.36
ROW6: D35.1, D40.1, D45.1, D50.1, D55.1, D60.1, D65.1, U2.37
ROW7: D36.1, D41.1, D46.1, D51.1, D56.1, D61.1, D66.1, U2.38
ROW8: D37.1, D42.1, D47.1, D52.1, D57.1, D62.1, D67.1, U2.11
ROW9: D38.1, D43.1, D48.1, D53.1, D58.1, D63.1, D68.1, U2.10
TRRS0: J1.3, J2.3, R2.1, R3.2, U1.18, U2.18, U4.6, U5.6
TRRS1: J1.2, J2.2, R1.1, R4.2, U1.19, U2.19, U4.4, U5.4
VCC: F1.2, F2.2, J3.A4, J3.A9, J3.B4, J3.B9, J4.A4, J4.A9, J4.B4, J4.B9

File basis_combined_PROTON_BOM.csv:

Id,Designator,Package,Quantity,Designation,Supplier and ref,LCSC Part #,
1,"MXop1,MX1,MX2,MX3,MX4,MXa1,MXc1,MXcm1,MXct1,MXd1,MXe1,MXf1,MXfn1,MXg1,MXq1,MXr1,MXs1,MXsp0,MXsp1,MXspC1,MXt1,MXv1,MXw1,MXx1,MXz1,MX`1,MXtb1,MXes1,MX5,MXb1,MXy1,MXup1,MXu1,MXtb[1,MXsp_rC1,MXsp_r1,MXsp_r0,MXright1,MXp1,MXo1,MXn1,MXm1,MXleft1,MXl1,MXk1,MXj1,MXi1,MXh1,MXdown1,MX`=1,MX`-1,MX]1,MX;1,MX/1,MX'1,MX9,MX8,MX7,MX6,MX,1,MX.1,MX0,MXsh_r1,MXdel1,MX\1,MXret1,MXsh1",Kailh_socket_MX_optional_FLIPPED,67,MX-NoLED,KAILH PCB SOCKET CPG151101S11,,
2,"D68,D67,D66,D65,D64,D63,D62,D61,D60,D59,D58,D57,D56,D55,D54,D53,D52,D51,D50,D49,D48,D47,D46,D45,D44,D43,D42,D41,D40,D39,D38,D37,D36,D35,D34,D33,D32,D31,D30,D29,D28,D27,D26,D25,D24,D23,D22,D21,D20,D19,D18,D17,D16,D15,D14,D13,D12,D11,D10,D9,D8,D7,D6,D5,D4,D3,D2,D1",D_SOD-323F,68,D_Small,,C2128,
3,"J2,J1,J4,J3",USB_Micro-B_Molex-105017-0001,4,USB_B_Micro,Molex 105017-001,,
6,"U2,U1",TQFP-44_10x10mm_P0.8mm,2,ATmega32U4-AU,,C44854,
7,"Y2,Y1",Crystal_SMD_3225-4Pin_3.2x2.5mm,2,Crystal_GND24_Small,,C13738,
8,"SW5,SW4",SKQG-1155865,2,SW_Push,,,
9,"R12,R11,R8,R7",R_0805_2012Metric,4,10k,,C17414,
10,"R10,R9,R6,R5",R_0805_2012Metric,4,22,,C17561,
11,"F2,F1",Fuse_1206_3216Metric,2,500mA,, C151162,
12,"C16,C14,C13,C8,C6,C5,C12,C4",C_0805_2012Metric,6,0.1uF,,C49678,
13,"C15,C7",C_0805_2012Metric,2,1uF,,C28323,
15,"C11,C10,C3,C2",C_0805_2012Metric,4,22uF,,C45783,
16,"C9,C1",C_0805_2012Metric,2,10uF,,C15850,
17,"R4,R3,R2,R1",R_0805_2012Metric,4,4.7k,,C17673,

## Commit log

2020-04-16 Created project
2020-04-16 Add submodules
2020-04-16 Add libs
2020-04-16 2x2 setup done
2020-04-28 l schema and pcb ver 1 ready
2020-04-30 v1 of the left side done
2020-05-02 dual protons 75%
2020-05-05 no proton v0 finished
2020-05-06 done with usbs
2020-05-07 version sent to pcb manu
2020-05-16 missed files? don't know'
2020-05-30 Added a bunch of cleanup etc
2020-06-23 checkpoint
2020-07-03 Yeah
2020-07-04 Add shield grounding, curves etc
2020-07-04 fix all the crossed labels
2020-07-04 shuffle the left amp
2020-09-05 v3 gerbers

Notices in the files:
parts and their libraries:
Copyright 2016 Accelerated Designs. All rights reserved.
